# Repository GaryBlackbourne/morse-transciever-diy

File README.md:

# DIY Morse transmitter

This project is a university project.

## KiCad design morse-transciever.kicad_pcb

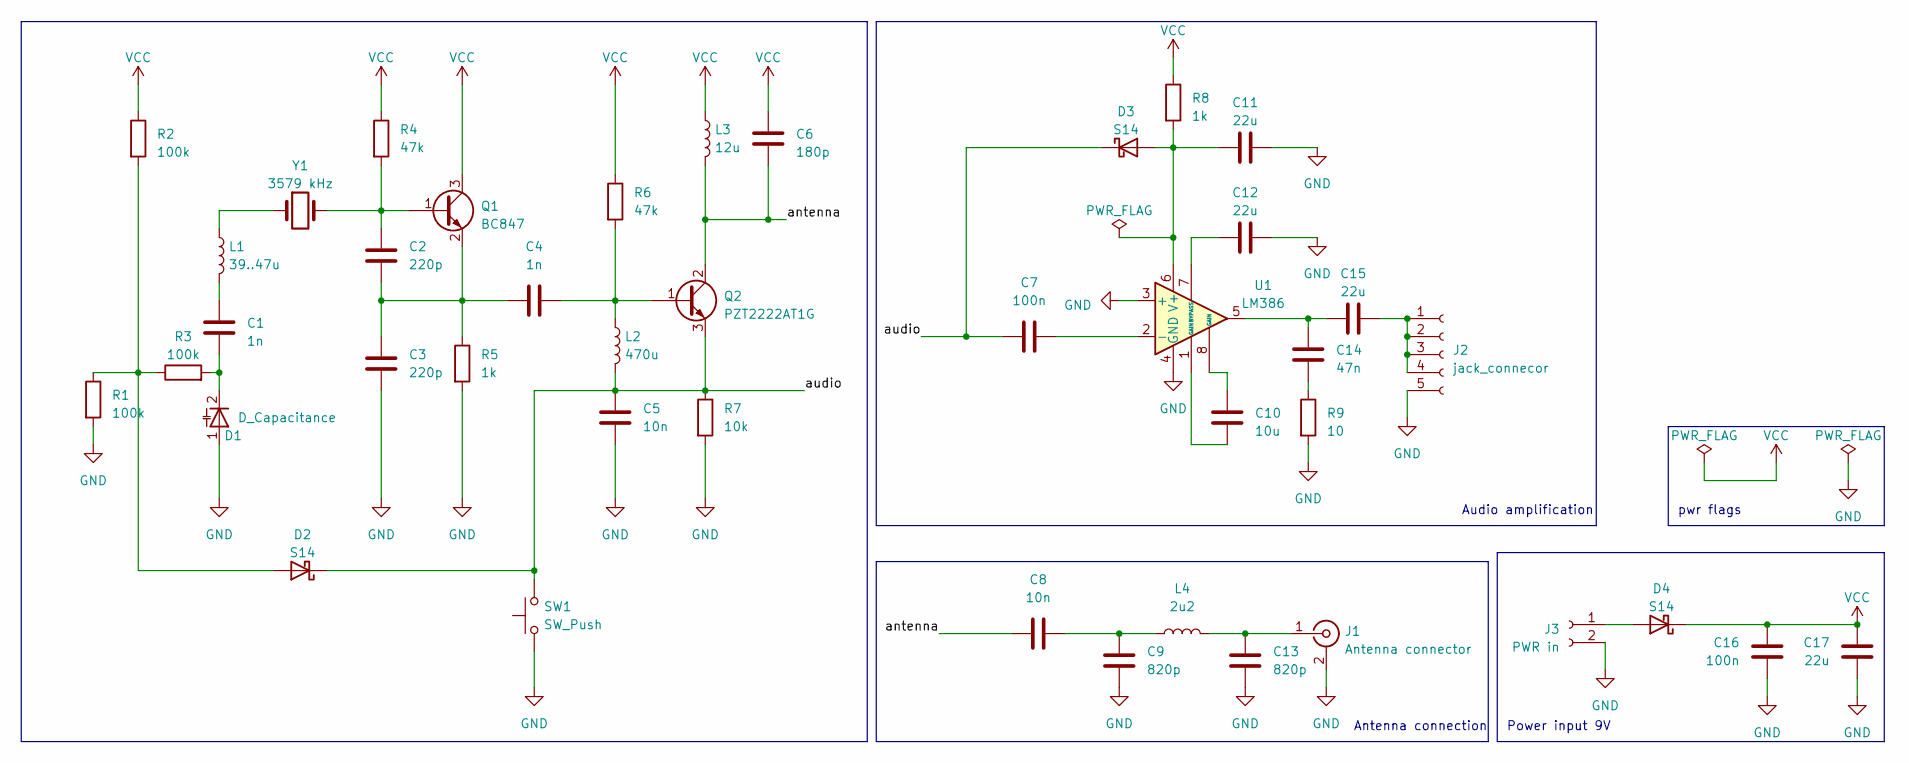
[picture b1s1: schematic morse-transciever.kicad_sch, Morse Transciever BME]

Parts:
C1, C4: 1n; C_0805_2012Metric_Pad1.18x1.45mm_HandSolder
C2, C3: 220p; C_0805_2012Metric_Pad1.18x1.45mm_HandSolder
C5, C8: 10n; C_0805_2012Metric_Pad1.18x1.45mm_HandSolder
C6: 180p; C_0805_2012Metric_Pad1.18x1.45mm_HandSolder
C7, C16: 100n; C_0805_2012Metric_Pad1.18x1.45mm_HandSolder
C9, C13: 820p; C_0805_2012Metric_Pad1.18x1.45mm_HandSolder
C10: 10u; C_0805_2012Metric_Pad1.18x1.45mm_HandSolder
C11, C12, C15, C17: 22u; C_0805_2012Metric_Pad1.18x1.45mm_HandSolder
C14: 47n; C_0805_2012Metric_Pad1.18x1.45mm_HandSolder
D1: D_Capacitance; SOT-223
D2, D3, D4: S14; D_SOD-123
J1: Antenna connector; sma_rf_connector
J2: jack_connecor; jack_audio_connector
J3: PWR in; PinHeader_1x02_P2.54mm_Vertical
L1: 39..47u; L_1210_3225Metric_Pad1.42x2.65mm_HandSolder
L2: 470u; L_1812_4532Metric_Pad1.30x3.40mm_HandSolder
L3: 12u; L_1210_3225Metric_Pad1.42x2.65mm_HandSolder
L4: 2u2; L_1210_3225Metric_Pad1.42x2.65mm_HandSolder
Q1: BC847; SOT-23
Q2: PZT2222AT1G; SOT-223
R1, R2, R3: 100k; R_0805_2012Metric_Pad1.20x1.40mm_HandSolder
R4, R6: 47k; R_0805_2012Metric_Pad1.20x1.40mm_HandSolder
R5, R8: 1k; R_0805_2012Metric_Pad1.20x1.40mm_HandSolder
R7: 10k; R_0805_2012Metric_Pad1.20x1.40mm_HandSolder
R9: 10; R_0805_2012Metric_Pad1.20x1.40mm_HandSolder
SW1: SW_Push; key
U1: LM386; SOIC-8_3.9x4.9mm_P1.27mm
Y1: 3579 kHz; Crystal_SMD_HC49-SD_HandSoldering

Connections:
/antenna: C6.2, C8.1, L3.2, Q2.2 (C)
/audio: C5.1, C7.1, D2.1 (K), D3.1 (K), L2.2, Q2.3 (E), R7.1, SW1.2
GND: C3.2, C5.2, C9.1, C11.2, C12.2, C13.2, C16.2, C17.2, D1.1 (K), J1.2 (Ext), J2.5, J3.2, R1.2, R5.2, R7.2, R9.2, SW1.1, U1.3 (+), U1.4 (GND)
unnamed: C1.1, L1.2
unnamed: C8.2, C9.2, L4.1
unnamed: C10.1, U1.8 (GAIN)
unnamed: C10.2, U1.1 (GAIN)
unnamed: C14.1, C15.1, U1.5
unnamed: C14.2, R9.1
unnamed: C1.2, D1.2 (A), R3.2
unnamed: D2.2 (A), R1.1, R2.2, R3.1
unnamed: C11.1, D3.2 (A), R8.2, U1.6 (V+)
unnamed: D4.2 (A), J3.1
unnamed: C13.1, J1.1 (In), L4.2
unnamed: C15.2, J2.1, J2.2, J2.3, J2.4
unnamed: L1.1, Y1.1
unnamed: C2.1, Q1.1 (B), R4.2, Y1.2
unnamed: C2.2, C3.1, C4.1, Q1.2 (E), R5.1
unnamed: C4.2, L2.1, Q2.1 (B), R6.2
unnamed: C7.2, U1.2 (-)
unnamed: C12.1, U1.7 (BYPASS)
VCC: C6.1, C16.1, C17.1, D4.1 (K), L3.1, Q1.3 (C), R2.1, R4.1, R6.1, R8.1

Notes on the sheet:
Antenna connection
pwr flags
Audio amplification
Power input 9V

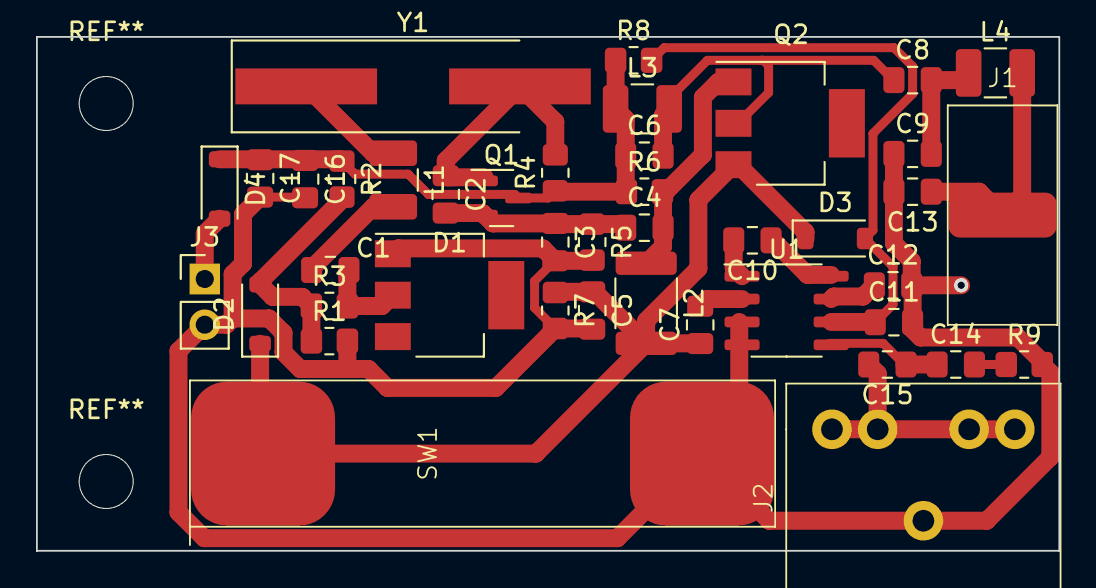
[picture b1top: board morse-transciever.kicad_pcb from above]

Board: 2 copper layers, 56.8 x 28.5 mm, 42 parts (0 on the bottom side), 22 nets.

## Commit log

2023-03-22 2023.03.22 class modifications
2023-03-22 Finalize schematic
2023-03-22 Finalize footprints
2023-03-31 2023.03.29 class modifications
2023-03-31 Remove unnecessary files
2023-03-31 Add readme
2023-04-19 Finalizing PCB design, ready for gerber generation
2023-05-03 Add parts list
